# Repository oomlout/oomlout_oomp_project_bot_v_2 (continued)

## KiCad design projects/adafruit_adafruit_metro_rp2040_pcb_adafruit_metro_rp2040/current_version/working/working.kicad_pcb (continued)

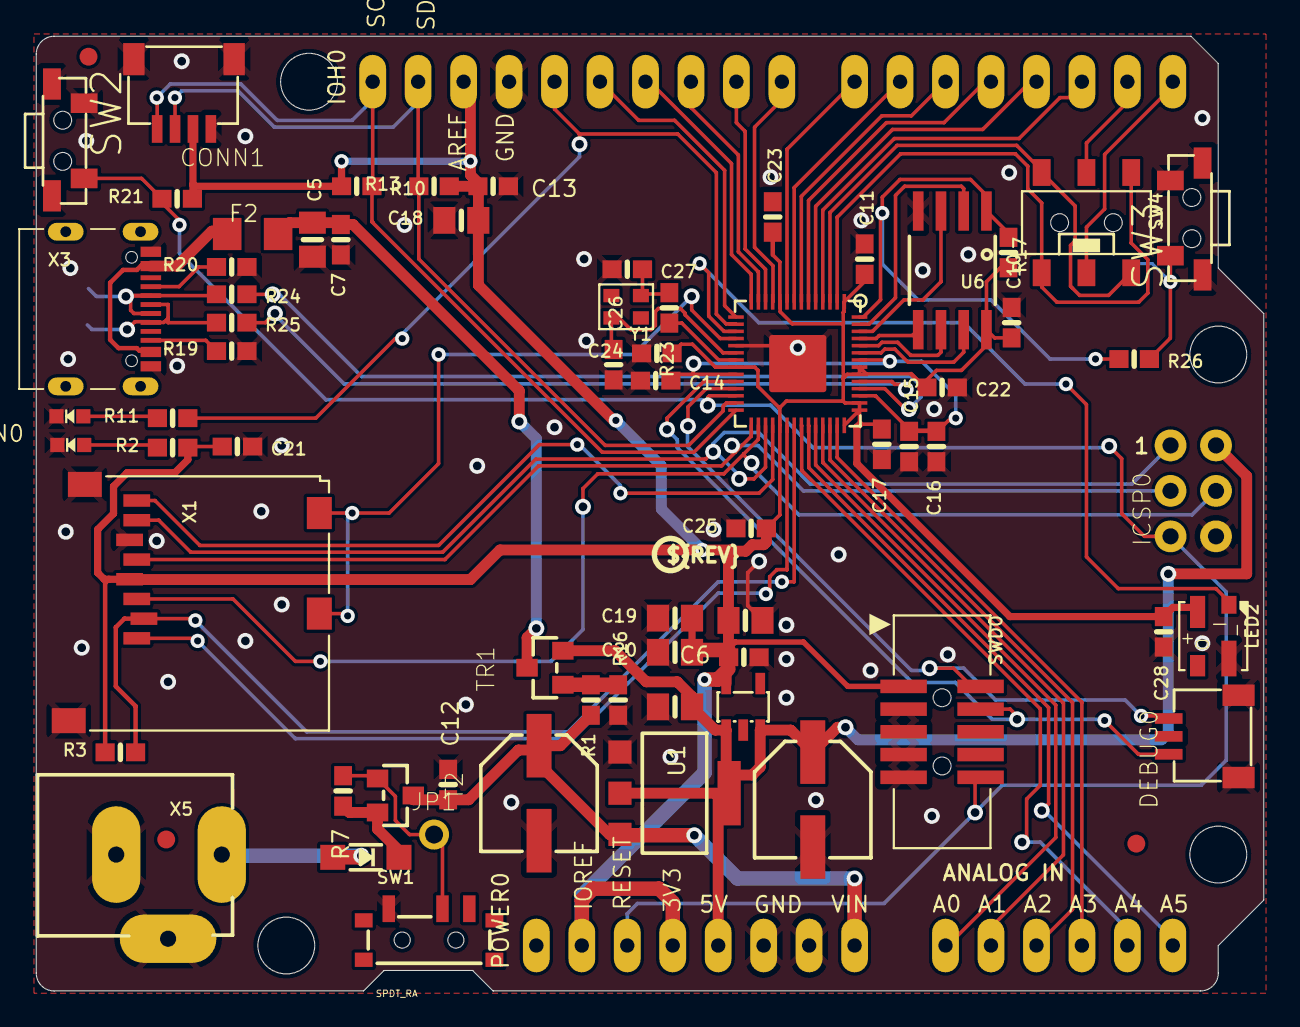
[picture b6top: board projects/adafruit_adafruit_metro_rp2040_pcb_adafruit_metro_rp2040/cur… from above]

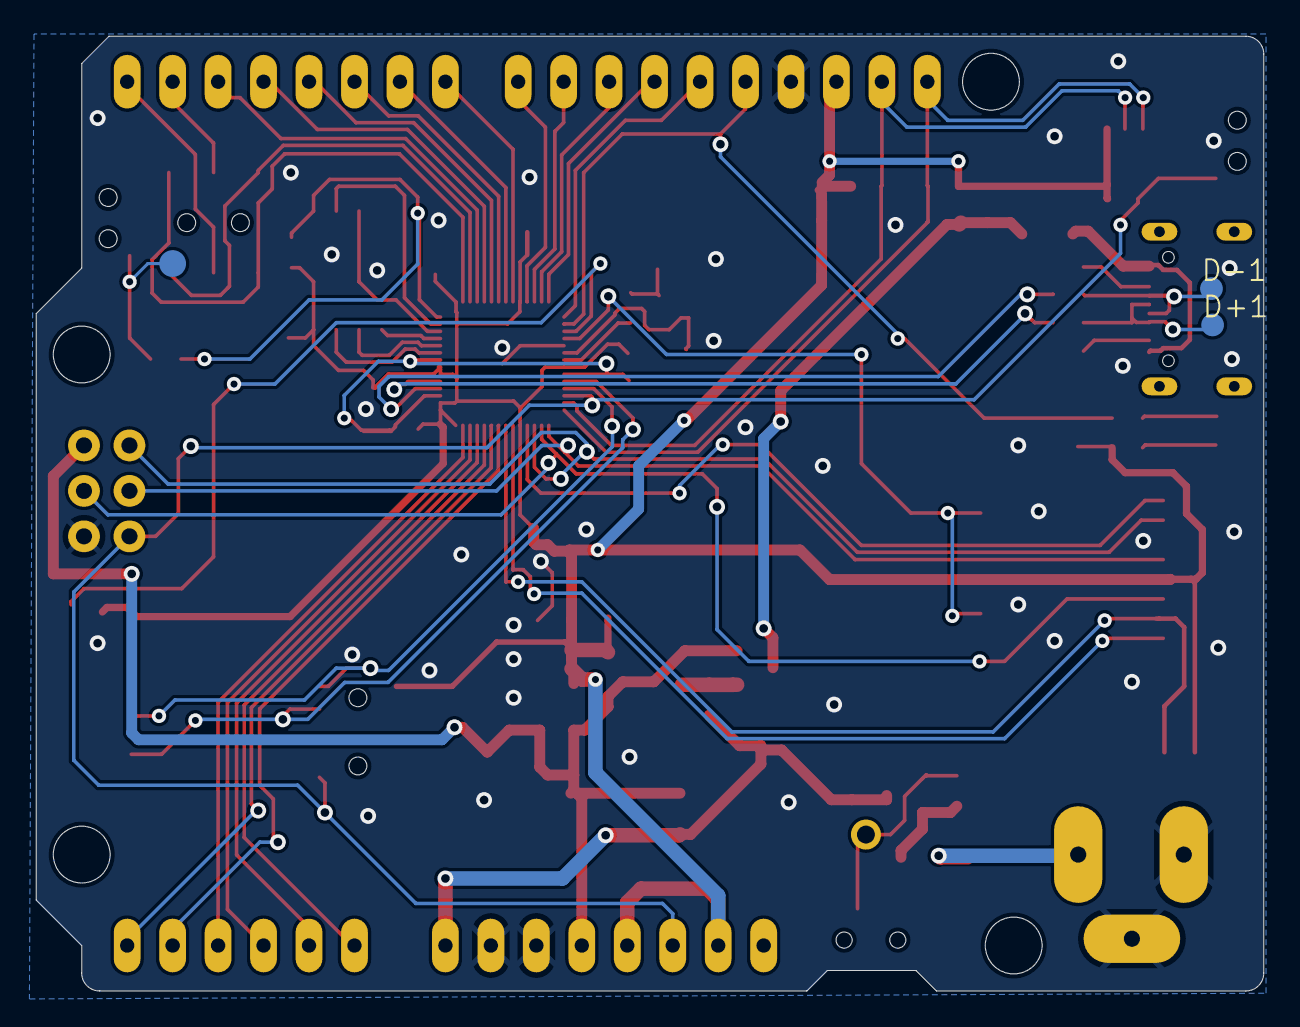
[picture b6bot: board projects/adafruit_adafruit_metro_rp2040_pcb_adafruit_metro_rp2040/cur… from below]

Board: 2 copper layers, 68.6 x 53.3 mm, 83 parts (4 on the bottom side), 64 nets.

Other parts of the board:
@HOLE0, @HOLE1, @HOLE2, @HOLE3: (no value)
U$11: PCBFEAT-REV-040
U$15: METRO_RP2040_BOT
U$29: METRO_RP2040_TOP

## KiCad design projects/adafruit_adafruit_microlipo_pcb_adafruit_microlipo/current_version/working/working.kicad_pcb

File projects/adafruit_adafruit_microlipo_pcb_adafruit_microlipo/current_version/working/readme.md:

# adafruit_microlipo_pcb
 
## summary 
* id: adafruit_adafruit_microlipo_pcb_adafruit_microlipo
* user: adafruit
* name: adafruit_microlipo_pcb
* board: adafruit_microlipo
* repo: https://github.com/adafruit/Adafruit-MicroLipo-PCB

* src_file_repo_sch: 
* src_file_repo_sch_link: https://github.com/adafruit/Adafruit-MicroLipo-PCB/tree/master/
* full details link: https://github.com/oomlout/oomlout_oomp_project_bot_v_2/tree/main/projects/adafruit_adafruit_microlipo_pcb_adafruit_microlipo/current_version/working  

## schematic  
  
[schematic (pdf)](working_schematic.pdf) 

## pcb  

[board (pdf)](working.pdf)  

## working_bom
| Id | Designator | Footprint | Quantity | Designation | Supplier and ref |  | None | 
| --- | --- | --- | --- | --- | --- | --- | --- | 
| 1 | C2,C1 | 0805-NO | 2 | 10uF |  |  | [''] | 
| 2 | PLABEL1 | PLABEL1 | 1 |  |  |  | [''] | 
| 3 | PLABEL4 | PLABEL4 | 1 |  |  |  | [''] | 
| 4 | PLABEL0 | PLABEL0 | 1 |  |  |  | [''] | 
| 5 | PLABEL7 | PLABEL7 | 1 |  |  |  | [''] | 
| 6 | SW1 | EG1390 | 1 | DPDT Switch |  |  | [''] | 
| 7 | R2,R3 | 0603-NO | 2 | 10K |  |  | [''] | 
| 8 | PLABEL5 | PLABEL5 | 1 |  |  |  | [''] | 
| 9 | PLABEL6 | PLABEL6 | 1 |  |  |  | [''] | 
| 10 | R1,R4 | 0603-NO | 2 | 2K |  |  | [''] | 
| 11 | FID1 | FIDUCIAL_1MM | 1 | FIDUCIAL_1MM |  |  | [''] | 
| 12 | X1 | USBA_PCB | 1 | PCBUSB |  |  | [''] | 
| 13 | PLABEL8 | PLABEL8 | 1 |  |  |  | [''] | 
| 14 | U1 | SOT23-5 | 1 | MCP73831T-2ACI/OT |  |  | [''] | 
| 15 | LED2 | CHIPLED_0603_NOOUTLINE | 1 | GREEN |  |  | [''] | 
| 16 | PLABEL3 | PLABEL3 | 1 |  |  |  | [''] | 
| 17 | PLABEL2 | PLABEL2 | 1 |  |  |  | [''] | 
| 18 | X3 | JSTPH2_BATT | 1 | CON_JST_PH_2PIN_MT_BATT |  |  | [''] | 
| 19 | LED1 | CHIPLED_0603_NOOUTLINE | 1 | RED |  |  | [''] | 
| 20 | U$9 | PCBFEAT-REV-040 | 1 |  |  |  | [''] | 
| 21 | U$8 | ADAFRUIT_TEXT_20MM | 1 |  |  |  | [''] | 
| 22 | PLABEL10 | PLABEL10 | 1 |  |  |  | [''] | 
| 23 | PLABEL9 | PLABEL9 | 1 |  |  |  | [''] | 
| 24 | PLABEL11 | PLABEL11 | 1 |  |  |  | [''] | 

## bom_schematic
| Ref | Qnty | Value | Cmp name | Footprint | Description | Vendor | DNP | 
| --- | --- | --- | --- | --- | --- | --- | --- | 
| C1, C2 | 2 | 10uF | CAP_CERAMIC0805-NOOUTLINE | working:0805-NO |  |  |  | 
| FID1 | 1 | FIDUCIAL_1MM | FIDUCIAL_1MM | working:FIDUCIAL_1MM |  |  |  | 
| LED1 | 1 | RED | LED0603_NOOUTLINE | working:CHIPLED_0603_NOOUTLINE |  |  |  | 
| LED2 | 1 | GREEN | LED0603_NOOUTLINE | working:CHIPLED_0603_NOOUTLINE |  |  |  | 
| R1, R4 | 2 | 2K | RESISTOR_0603_NOOUT | working:0603-NO |  |  |  | 
| R2, R3 | 2 | 10K | RESISTOR_0603_NOOUT | working:0603-NO |  |  |  | 
| SW1 | 1 | DPDT Switch | SWITCH_DPDTEG1390 | working:EG1390 |  |  |  | 
| U1 | 1 | MCP73831T-2ACI/OT | MCP73831/2 | working:SOT23-5 |  |  |  | 
| X1 | 1 | PCBUSB | USB_TYPEAPCB | working:USBA_PCB |  |  |  | 
| X3 | 1 | CON_JST_PH_2PIN_MT_BATT | CON_JST_PH_2PIN_MT_BATT | working:JSTPH2_BATT |  |  |  |

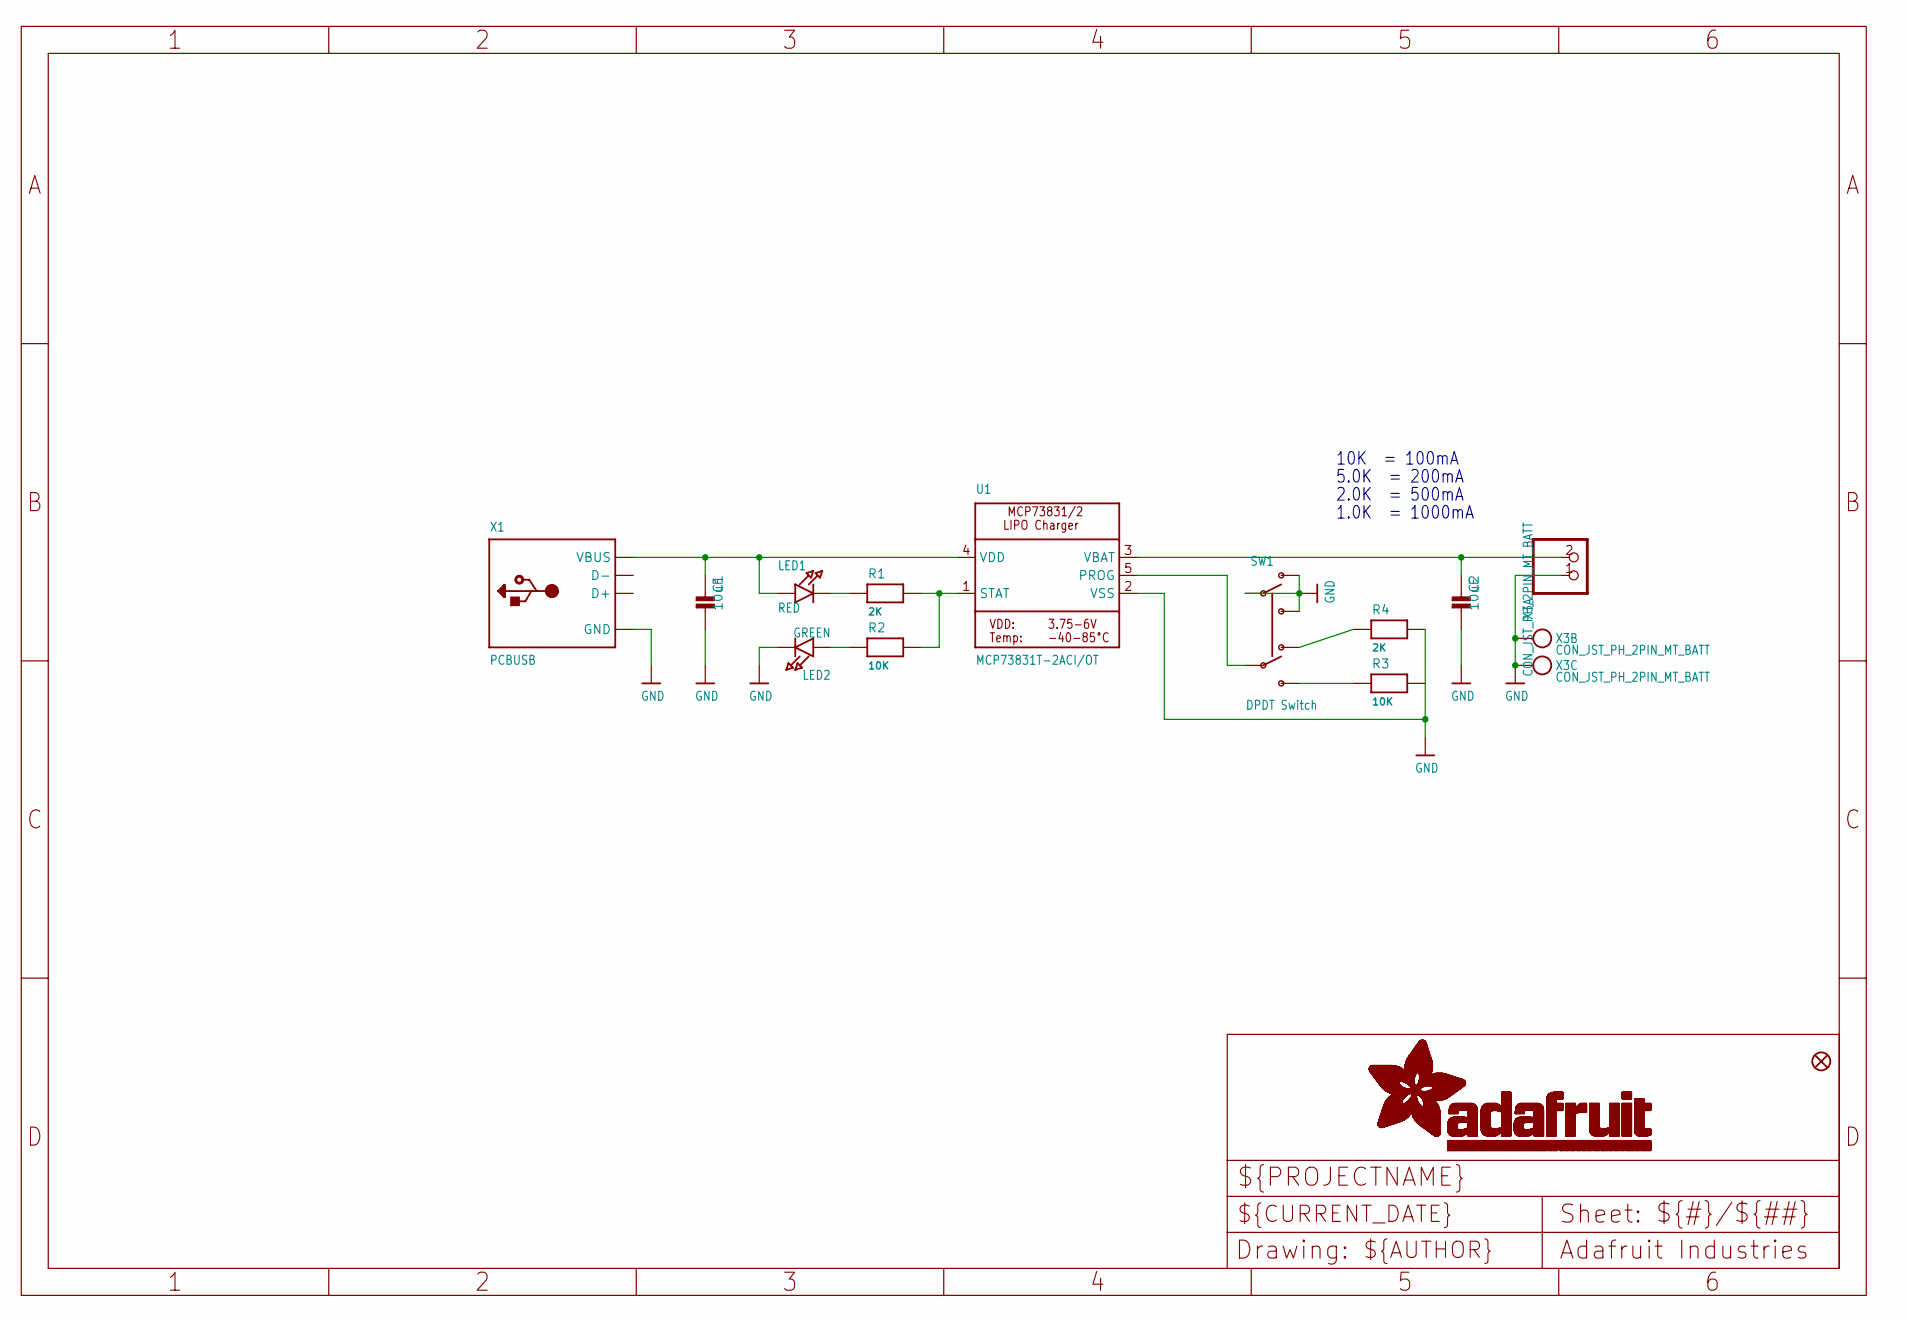
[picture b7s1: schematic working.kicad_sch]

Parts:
C1, C2: 10uF; 0805-NO
FID1: FIDUCIAL_1MM
LED1: RED; CHIPLED_0603_NOOUTLINE
LED2: GREEN; CHIPLED_0603_NOOUTLINE
R1, R4: 2K; 0603-NO
R2, R3: 10K; 0603-NO
SW1: DPDT Switch; EG1390
U1: MCP73831T-2ACI/OT; SOT23-5
X1: PCBUSB; USBA_PCB
X3: CON_JST_PH_2PIN_MT_BATT; JSTPH2_BATT

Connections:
GND: C1.2, C2.2, LED2.C, R3.2, R4.2, SW1.O1, SW1.P1, SW1.S1, U1.2 (VSS), X1.GND, X3.1, X3.NC1, X3.NC2
unnamed: LED1.C, R1.1
unnamed: R1.2, R2.2, U1.1 (STAT)
unnamed: R3.1, SW1.S2
unnamed: R4.1, SW1.O2
unnamed: SW1.P2, U1.5 (PROG)
unnamed: LED2.A, R2.1
VBAT: C2.1, U1.3 (VBAT), X3.2
VDD: C1.1, LED1.A, U1.4 (VDD), X1.VCC (VBUS)

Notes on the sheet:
2.0K = 500mA
10K = 100mA
1.0K = 1000mA
5.0K = 200mA

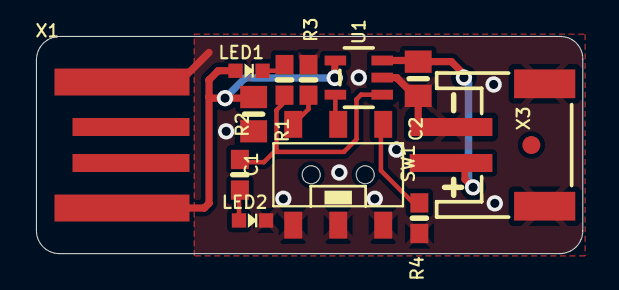
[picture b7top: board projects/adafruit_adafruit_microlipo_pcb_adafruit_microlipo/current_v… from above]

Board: 2 copper layers, 30.4 x 12.1 mm, 27 parts (5 on the bottom side), 9 nets.

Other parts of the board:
PLABEL0: PLABEL0
PLABEL1: PLABEL1
PLABEL2: PLABEL2
PLABEL3: PLABEL3
PLABEL4: PLABEL4
PLABEL5: PLABEL5
PLABEL6: PLABEL6
PLABEL7: PLABEL7
PLABEL8: PLABEL8
PLABEL9: PLABEL9
PLABEL10: PLABEL10
PLABEL11: PLABEL11
U$8: ADAFRUIT_TEXT_20MM
U$9: PCBFEAT-REV-040
